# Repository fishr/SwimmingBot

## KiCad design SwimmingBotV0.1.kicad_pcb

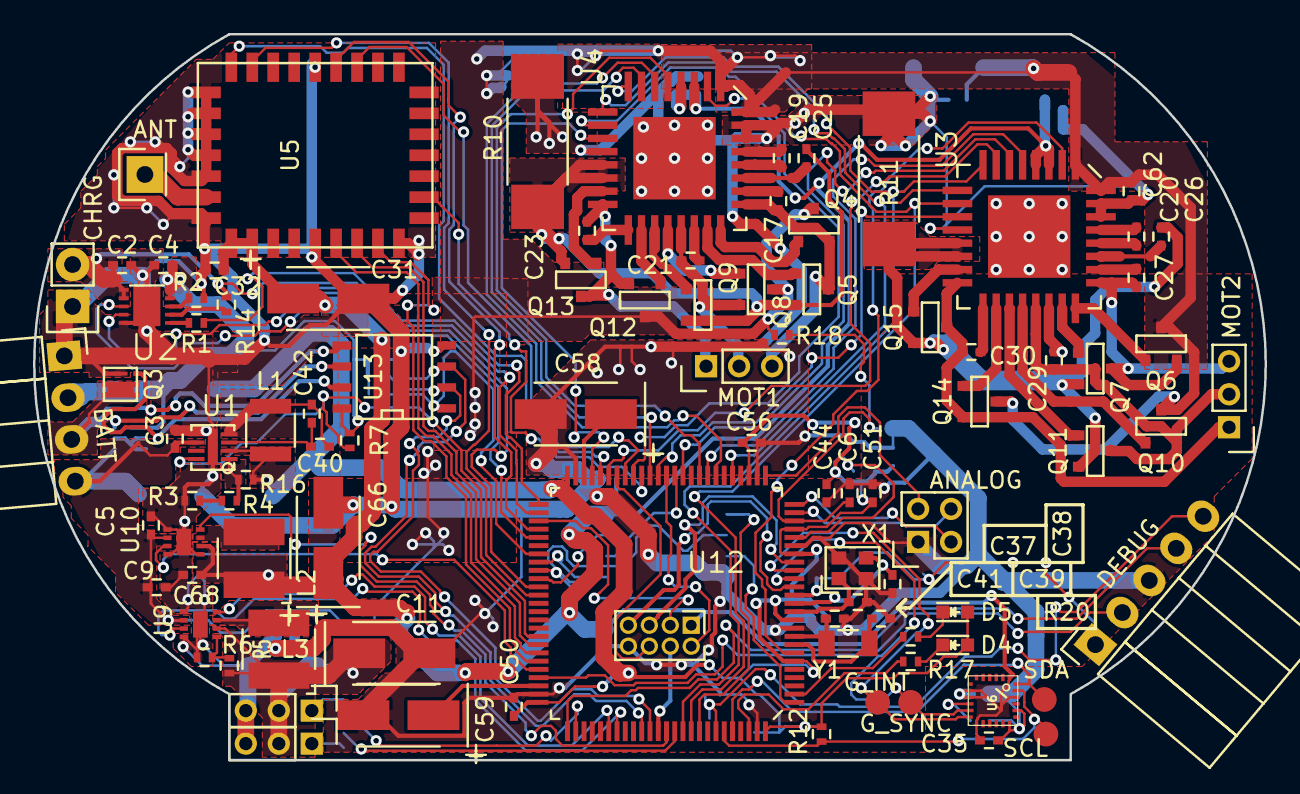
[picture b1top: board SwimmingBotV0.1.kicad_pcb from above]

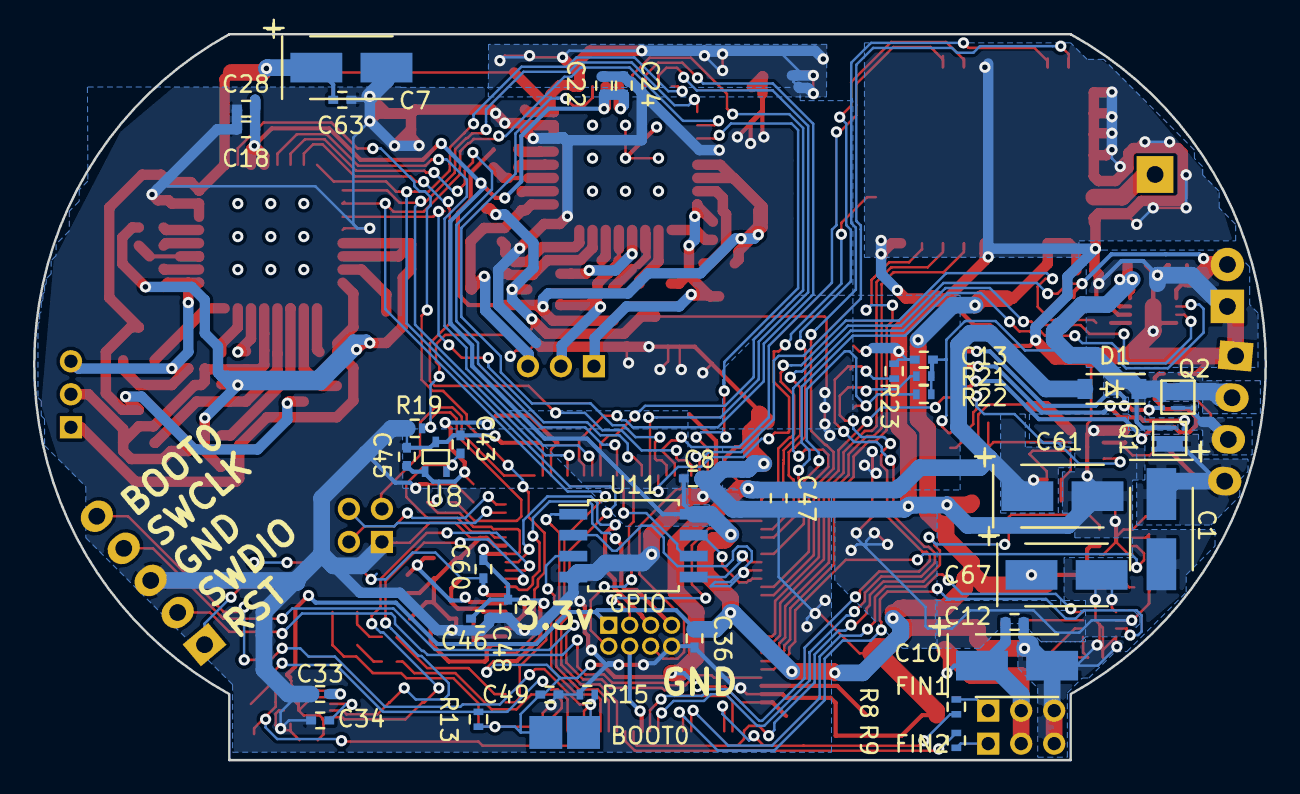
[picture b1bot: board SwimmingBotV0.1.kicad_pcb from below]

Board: 2 copper layers, 74.7 x 44.0 mm, 131 parts (37 on the bottom side), 126 nets.

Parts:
C1, C7, C10, C11, C31, C66, C67: 10uF; TantalC_SizeB_EIA-3528_HandSoldering
C2, C3, C4, C6, C12, C19, C20, C25, C26, C43, C62, C63, C68: 1uF; C_0402
C5, C8, C9, C13, C17, C18, C21, C22, C23, C24, C27, C28, C29, C30, C32, C33, C34, C35, C36, C40, C42, C44, C45, C46, C47, C48, C49, C50, C51, C56, C60: 100nF; C_0402
C37, C38, C39, C41: 10pF; C_0402
C58, C59: 2.2uF; TantalC_SizeB_EIA-3528_HandSoldering
C61: 10uF, <150mOhm; TantalC_SizeB_EIA-3528_HandSoldering
D1: ZENER; SOD-123
D4, D5: LED; LED_0603
JP1: BOOT0; SOLDER-JUMPER
L1: 10uH Isat 400mA; R_1210
L2, L3: 2.2uH; NR4018
P2: ANALOG; Pin_Header_Straight_2x02_Pitch2.00mm
P3: CHRG; Socket_Strip_Straight_1x02
P4: BATT; Socket_Strip_Angled_1x04
P5: GPIO; Pin_Header_Straight_2x04_Pitch1.27mm
P6: FIN1; Pin_Header_Straight_1x03_Pitch2.00mm
P7: FIN2; Pin_Header_Straight_1x03_Pitch2.00mm
P8: MOT1; Pin_Header_Straight_1x03_Pitch2.00mm
P9: MOT2; Pin_Header_Straight_1x03_Pitch2.00mm
P10: ANT; Socket_Strip_Straight_1x01
P11: DEBUG; Socket_Strip_Angled_1x05
Q1, Q2, Q3: Q_NMOS_DGS; SC-70-ENHANCED-DGS
Q4, Q5, Q6, Q7, Q8, Q9, Q10, Q11, Q12, Q13, Q14, Q15: PMV45EN2; SOT-23
R1: 5k; R_0402
R2, R3, R4, R6, R7, R14, R18, R21, R22, R23: 10k; R_0402
R5: 65k; R_0402
R8, R9: 100; R_0402
R10, R11: 0.1; R_2512_HandSoldering
R12, R13: 4k; R_0402
R15: 10K; R_0402
R16: 33k; R_0402
R17, R20: 1k; R_0402
R19: 4.1k-3.9k; R_0402
U1: LT3470A; DFN-8-3x2-THERM-.5MM
U2: MCP73834; DFN-10-THERM-.5MM
U3, U4: A4960; LQFP_32_THERM_.8MM
U5: HUM-900-PRO
U6: MPU-9250
U8: MAX6034_25; SC-70-3
U9, U10: TPS6216X; WSON-8
U11: SST26VF064B; SOIJ-8_5.3x5.3mm_Pitch1.27mm
U12: STM32F446-100; STM32F446_QFP_100
U13: LTC1163; SOIC-8-N
W1: G_SYNC; Measurement_Point_Round-SMD-Pad_Small
W2: G_INT; Measurement_Point_Round-SMD-Pad_Small
W4: SDA; Measurement_Point_Round-SMD-Pad_Small
W5: SCL; Measurement_Point_Round-SMD-Pad_Small
X1: CRYSTAL_SMD; SMD_XTAL_2.5x2MM
Y1: Crystal; SMD_XTAL_3.2x1.5MM

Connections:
/Charge/1S: C4.1, C13.1, D1.1, P4.2, Q1.3, Q2.1, R7.1, R21.2, R22.2, U2.9, U2.10, U13.8
/Charge/2S: C1.1, C3.2, C5.1, C7.1, C9.1, C62.1, C63.1, P4.4, Q1.1, Q4.3, Q6.3, Q8.3, Q10.3, Q12.3, Q14.3, R18.1, U1.6, U3.1, U3.32, U4.1, U4.32, U9.2, U10.2
/Charge/2S_NEG: P4.3, Q2.3, Q3.1
/Charge/5V_CHG: C2.1, P3.2, R14.1, U2.1, U2.2, U12.52
/Charge/BATT_SEL1: R22.1, U12.57, U13.1
/Charge/BATT_SEL2: R21.1, U12.86, U13.2
/Charge/BATT_SEL3: R23.2, U12.85, U13.3
/Charge/CHG_EN#: R1.1, U12.51
/Charge/CHG_STAT1: U2.3, U12.55
/Charge/CHG_STAT2: U2.4, U12.61
/Charge/GATE1: Q3.2, U13.7
/Charge/GATE2: Q1.2, U13.6
/Charge/GATE3: Q2.2, U13.5
/Digital/3.3V: C8.2, C18.2, C22.2, C24.2, C28.2, C31.1, C32.1, C33.1, C35.2, C36.1, C66.1, C67.1, C68.2, L2.1, P5.1, U3.3, U3.4, U4.3, U4.4, U5.21, U5.22, U6.1, U6.8, U6.9, U6.13, U6.22, U10.6, U11.8
/Digital/CE#: U11.1, U12.92
/Micro/A0: C6.1, R18.2, R19.1, U12.23
/Micro/A1: P2.4, U12.24
/Micro/A2: P2.3, U12.25
/Micro/A3: P2.2, U12.26
/Micro/BOOT0: JP1.2, P11.5, R15.1, U12.94
/Micro/HS_X1: C37.1, U12.12, X1.1
/Micro/HS_X2: C38.1, U12.13, X1.2
/Micro/MOT1_PWM: U4.6, U12.32
/Micro/MOT2_PWM: U3.6, U12.36
/Micro/PA8: R7.2, U1.8, U12.67
/Micro/PB14: P5.3, U12.53
/Micro/PB15: U5.8, U12.54
/Micro/PC0: P5.7, U12.15
/Micro/PC3: P5.5, U12.18
/Micro/PD0: U9.8, U12.81
/Micro/PD1: U9.3, U12.82
/Micro/PD6: P5.4, U12.87
/Micro/PD15: U5.12, U12.62
/Micro/PE1: R17.2, U12.98
/Micro/PE3: R20.2, U12.2
/Micro/PE7: P5.2, U12.38
/Micro/PE10: U5.31, U12.41
/Micro/PE12: U5.7, U12.43
/Micro/PE13: P5.6, U12.44
/Micro/PE15: U5.13, U12.46
/Micro/QUADSPI_CLK: U11.6, U12.37
/Micro/QUADSPI_IO0: U11.5, U12.58
/Micro/QUADSPI_IO1: U11.2, U12.59
/Micro/QUADSPI_IO2: U11.3, U12.1
/Micro/QUADSPI_IO3: U11.7, U12.60
/Micro/RST#: C60.2, P11.1, U12.14
/Micro/SCL: R12.2, U6.23, U12.95, W5.1
/Micro/SDA: R13.2, U6.24, U12.96, W4.1
/Micro/SWCLK: P11.4, U12.76
/Micro/SWDIO: P11.2, U12.72
/Micro/VCAP_1: C58.1, U12.48
/Micro/VCAP_2: C59.1, U12.73
/Micro/VREF: C43.1, U8.2, U12.21
/Micro/X1: C39.1, U12.8, Y1.2
/Micro/X2: C41.1, U12.9, Y1.1
/Motors/A1: C17.2, P8.3, Q4.2, Q5.3, U4.25
/Motors/A2: C27.2, P9.3, Q6.2, Q7.3, U3.25
/Motors/B1: C21.2, P8.2, Q8.2, Q9.3, U4.21
/Motors/B2: C29.2, P9.2, Q10.2, Q11.3, U3.21
/Motors/C1: C23.2, P8.1, Q12.2, Q13.3, U4.16
/Motors/C2: C30.2, P9.1, Q14.2, Q15.3, U3.16
/Motors/CA1: C17.1, U4.26
/Motors/CA2: C27.1, U3.26
/Motors/CB1: C21.1, U4.22
/Motors/CB2: C29.1, U3.22
/Motors/CC1: C23.1, U4.17
/Motors/CC2: C30.1, U3.17
/Motors/CP11: C19.2, U4.28
/Motors/CP12: C20.2, U3.28
/Motors/CP21: C19.1, U4.29
/Motors/CP22: C20.1, U3.29
/Motors/FIN1: R8.2, U12.77
/Motors/FIN2: R9.2, U12.89
/Motors/GHA: Q4.1, U4.24
/Motors/GHA2: Q6.1, U3.24
/Motors/GHB: Q8.1, U4.20
/Motors/GHB2: Q10.1, U3.20
/Motors/GHC: Q12.1, U4.18
/Motors/GHC2: Q14.1, U3.18
/Motors/GLA: Q5.1, U4.23
/Motors/GLA2: Q7.1, U3.23
/Motors/GLB: Q9.1, U4.19
/Motors/GLB2: Q11.1, U3.19
/Motors/GLC: Q13.1, U4.15
/Motors/GLC2: Q15.1, U3.15
/Motors/LSS: C25.1, Q5.2, Q9.2, Q13.2, R10.1, U4.13, U4.14
/Motors/LSS2: C26.1, Q7.2, Q11.2, Q15.2, R11.1, U3.13, U3.14
/Motors/MOT1_CS#: U4.11, U12.47
/Motors/MOT1_DIAG: U4.5, U12.34
/Motors/MOT1_RESET#: U4.2, U12.42
/Motors/MOT1_TACH: U4.7, U12.40
/Motors/MOT2_CS#: U3.11, U12.39
/Motors/MOT2_DIAG: U3.5, U12.33
/Motors/MOT2_RESET#: U3.2, U12.7
/Motors/MOT2_TACH: U3.7, U12.45
/Motors/SCK: U3.9, U4.9, U12.30
/Motors/SDI: U3.10, U4.10, U12.91
/Motors/SDO: U3.8, U4.8, U12.90
/Motors/VFIN: C10.1, C11.1, C12.2, L3.1, P6.2, P7.2, R5.1, U9.6
/Motors/VREG1: C25.2, U4.27
/Motors/VREG2: C26.2, U3.27
/Power/AUX_3.3V_EN: U10.3, U12.71
/Power/AUX_3.3V_GOOD: U10.8, U12.88
/Power/CHG_CTL_VCC: C44.1, C45.1, C46.1, C47.1, C48.1, C49.1, C50.1, C51.1, C56.1, C60.1, C61.1, D1.2, D4.2, D5.2, JP1.1, L1.1, R12.1, R13.1, R16.1, U1.2, U8.1, U12.6, U12.11, U12.19, U12.22, U12.28, U12.50, U12.75, U12.100
/Sensors/GYRO_FSYNC: U6.11, U12.16, W1.1
/Sensors/GYRO_INT: U6.12, U12.17, W2.1
/rf/RF_CTS: U5.28, U12.70
/rf/RF_RX: U5.27, U12.68
/rf/RF_TX: U5.26, U12.69
GND: C1.2, C2.2, C3.1, C4.2, C5.2, C6.2, C7.2, C8.1, C9.2, C10.2, C11.2, C12.1, C13.2, C18.1, C22.1, C24.1, C28.1, C31.2, C32.2, C33.2, C34.2, C35.1, C36.2, C37.2, C38.2, C39.2, C41.2, C43.2, C44.2, C45.2, C46.2, C47.2, C48.2, C49.2, C50.2, C51.2, C56.2, C58.2, C59.2, C61.2, C62.2, C63.2, C66.2, C67.2, C68.1, P2.1, P3.1, P4.1, P5.8, P6.3, P7.3, P11.3, Q3.3, R2.2, R3.2, R6.1, R10.2, R11.2, R15.2, R19.2, R23.1, U1.5, U2.5, U3.12, U3.30, U3.31, U4.12, U4.30, U4.31, U5.9, U5.14, U5.15, U5.16, U5.17, U5.18, U5.20, U5.25, U5.29, U6.18, U6.20, U8.3, U9.1, U9.4, U10.1, U10.4, U10.5, U11.4, U12.10, U12.20, U12.27, U12.49, U12.74, U12.99, U13.4, X1.3
unnamed: C34.1, U6.10
unnamed: C40.1, C42.1, L1.2, U1.4
unnamed: C40.2, C42.2, U1.3
unnamed: D4.1, R17.1
unnamed: D5.1, R20.1
unnamed: L2.2, U10.7
unnamed: L3.2, U9.7
unnamed: P6.1, R8.1
unnamed: P7.1, R9.1
unnamed: P10.1, U5.19
unnamed: R1.2, U2.6
unnamed: R2.1, U2.8
unnamed: R3.1, R4.2
unnamed: R5.2, R6.2, U9.5
unnamed: R14.2, U2.7
unnamed: R4.1, R16.2, U1.1

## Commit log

2016-05-02 initial, with rev 1 circuit schematic-ed, not laid out
2016-05-04 pcb going, almost done with memory chips
2016-05-04 pcb going, I think done with memory chips
2016-05-04 hoh, working on power stuffs now
2016-05-11 woohoo getting there
2016-05-11 done with connections, just needs plane cleanup
2016-05-12 PCB layout rev 1 done
2016-05-12 jk silkscreen is a mess still
2016-05-12 silkscreen and mask layers fixed, working on paste
2016-05-12 paste good
2016-07-21 added specs doc
2016-07-21 not final, moving towards board v0.2
2016-07-22 should have added the code as a submodule
2016-07-22 added pipe examples as a submodule, much better now
2016-07-22 some final file adds to get this repo fixed up
2016-07-22 removed old ram and flash, added new flash, switched to 100 pin micro
2016-07-22 swapped out battery serializing hardware from discrete to IC, and standard level fets
2016-07-25 potentially done with parts removal and reselection, on to pcb layout
2016-07-25 copied old pcb as starting point
2016-07-25 sketched board outline layer, it is currently conservative. Also removed obvious offenders from previous layout
2016-07-26 pcb started in earnest, footprint changes in schematics, about to rename v0.2 boardfile to v0.1, kicad needs the same filename to have backrefs for net highlighting
2016-07-26 swapped v0.2 pcb to v0.1 pcb since kicad doesn't like different file names
2016-07-26 some pin swaps for routing, done with power section
2016-07-26 commit before I go home
2016-07-27 rearranged inputs to all be available for unique interrupts, put unused GPIO on a header for later use
2016-07-27 autosave
2016-07-27 end of day, two lines left to connect
2016-07-28 different solder bridge, done with routing, moving silk layer around now
2016-07-29 submitted to fab woohoo
